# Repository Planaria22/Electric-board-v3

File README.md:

# Electric-board-v3
2026年高専祭で展示する予定の電光掲示板です

# 概要
32 * 32ドットのマトリクスが搭載されたドライバ基板を4枚横につなげることで32 * 128ドットの電光掲示板にする。ドライバ基板のジャンパ(JP1,JP2)を繋げば輝度調整も技術的には可能

# 使用技術
- MD1516C2-RG ドットマトリクスLED
  赤色と緑色のアノードコモン2色16×16LEDマトリクス。同時点灯を行うと赤緑橙の3色点灯が可能。このマトリクスをドライバ基板1枚に4個配置し、ドライバ基板を直列につなげることで32×128ドットの電光掲示板を作成する。
- 74HC595
  8bitシフトレジスタ。カスケード接続され、マイコンから送られたシリアル信号をパラレル信号へ変換する。
- PchMOSFET
  大電流が流れるアノード側スイッチング用。アクティブLowであることに注意。
- ダイナミック点灯
  電流を流すアノード(行)を変え続けることで使用するピン数と電流を削減する。
- PIO
  Programmable I/O。Raspberry Pi Picoに搭載されたピンの操作に特化したプロセッサ。PicoのCPUとは分離されており、1クロック単位でピンの入出力を制御できる。
- DMA
  Direct Memory Access。Raspberry Pi PicoのメモリとPIOをCPUを介せず高速に転送する。

# ピンアサイン
ドライバ基板の端子アサイン
## 6pinピンヘッダ・ソケット(QI)
```
+---+---+=======+---+---+
| 1 | 2 | 3 | 4 | 5 | 6 |
+---+---+---+---+---+---+
```
※デフォルトでは基板側のOEピンはプルダウンされています。使用する場合はドライバ基板のJP1かJP2、あるいは両方のジャンパを短絡してください。
1. アノードデータ
2. 赤色LEDカソードデータ
3. 緑色LEDカソードデータ
4. 74HC595 シフトレジスタクロック(SRCLK)
5. 74HC595 ストレージレジスタークロック(RCLK)
6. 74HC595 アウトプットエネーブル(OE)

## 電源ピン(VHコネクタ)
```
+=======+
| 1 | 2 |
+---+---+
```
※ドットマトリクス側が下
1. 5V電源+
2. GND電源-

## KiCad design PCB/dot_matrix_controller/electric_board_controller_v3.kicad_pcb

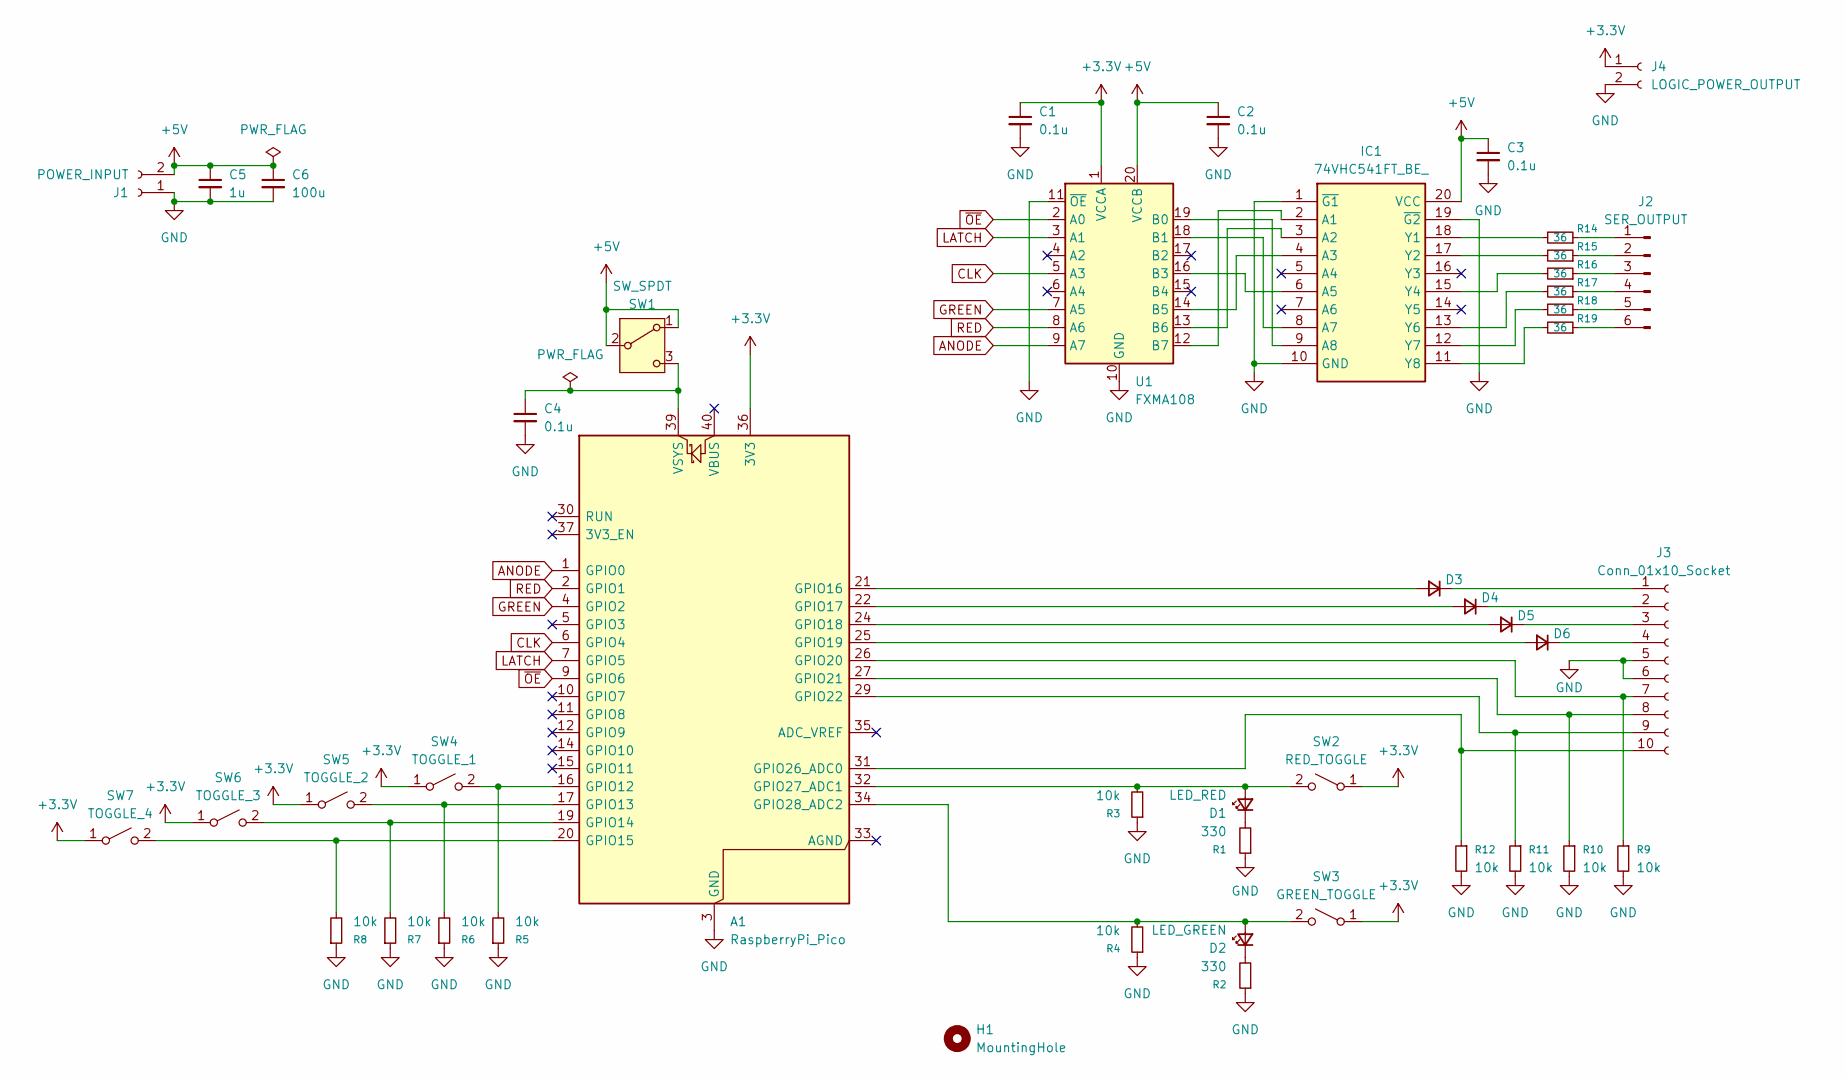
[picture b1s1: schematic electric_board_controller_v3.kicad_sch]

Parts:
A1: RaspberryPi_Pico; RaspberryPi_Pico_Common_Unspecified
C1, C2, C3, C4: 0.1u; C_Disc_D5.0mm_W2.5mm_P2.50mm
C5: 1u; C_Disc_D5.0mm_W2.5mm_P2.50mm
C6: 100u; CP_Radial_D5.0mm_P2.00mm
D1: LED_RED; LED_D2.0mm_W4.0mm_H2.8mm_FlatTop
D2: LED_GREEN; LED_D2.0mm_W4.0mm_H2.8mm_FlatTop
D3, D4, D5, D6: D_Small; D_DO-34_SOD68_P5.08mm_Vertical_AnodeUp
H1: MountingHole; MountingHole_3.2mm_M3
IC1: 74VHC541FT_BE_; 74VHC541FT(BE); Manufacturer_Part_Number 74VHC541FT(BE); Mouser Part Number 757-74VHC541FT(BE)
J1: POWER_INPUT; JST_VH_B2P-VH-B_1x02_P3.96mm_Vertical
J2: SER_OUTPUT; PinHeader_1x06_P2.54mm_Horizontal
J3: Conn_01x10_Socket; PinSocket_1x10_P2.54mm_Vertical
J4: LOGIC_POWER_OUTPUT; PinSocket_1x02_P2.54mm_Vertical
R1, R2: 330; R_Axial_DIN0207_L6.3mm_D2.5mm_P10.16mm_Horizontal
R3, R4, R5, R6, R7, R8: 10k; R_Axial_DIN0207_L6.3mm_D2.5mm_P10.16mm_Horizontal
R9, R10, R11, R12: 10k; R_0603_1608Metric
R14, R15, R16, R17, R18, R19: 36; R_0603_1608Metric
SW1: SW_SPDT; SW_Slide-03_Wuerth-WS-SLTV_10x2.5x6.4_P2.54mm
SW2: RED_TOGGLE; SW_Slide-02_Wuerth-WS-SLTV_10x2.5x6.4_P2.54mm
SW3: GREEN_TOGGLE; SW_Slide-02_Wuerth-WS-SLTV_10x2.5x6.4_P2.54mm
SW4: TOGGLE_1; SW_Slide-02_Wuerth-WS-SLTV_10x2.5x6.4_P2.54mm
SW5: TOGGLE_2; SW_Slide-02_Wuerth-WS-SLTV_10x2.5x6.4_P2.54mm
SW6: TOGGLE_3; SW_Slide-02_Wuerth-WS-SLTV_10x2.5x6.4_P2.54mm
SW7: TOGGLE_4; SW_Slide-02_Wuerth-WS-SLTV_10x2.5x6.4_P2.54mm
U1: FXMA108; FXMA108-DIP

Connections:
+3.3V: A1.36 (3V3), C1.1, J4.1, SW2.1 (A), SW3.1 (A), SW4.1 (A), SW5.1 (A), SW6.1 (A), SW7.1 (A), U1.1 (VCCA)
+5V: C2.1, C3.1, C5.1, C6.1, IC1.20 (VCC), J1.2, SW1.1 (A), SW1.2 (B), U1.20 (VCCB)
ANODE: A1.1 (GPIO0), U1.9 (A7)
CLK: A1.6 (GPIO4), U1.5 (A3)
GND: A1.3 (GND), A1.8 (GND), A1.13 (GND), A1.18 (GND), A1.23 (GND), A1.28 (GND), A1.38 (GND), C1.2, C2.2, C3.2, C4.2, C5.2, C6.2, IC1.1 (~G1), IC1.10 (GND), IC1.19 (~G2), J1.1, J3.5, J3.6, J4.2, R1.1, R2.1, R3.1, R4.1, R5.1, R6.1, R7.1, R8.1, R9.2, R10.2, R11.2, R12.2, U1.10 (GND), U1.11 (~OE)
GREEN: A1.4 (GPIO2), U1.7 (A5)
LATCH: A1.7 (GPIO5), U1.3 (A1)
unnamed: A1.16 (GPIO12), R5.2, SW4.2 (B)
unnamed: A1.17 (GPIO13), R6.2, SW5.2 (B)
unnamed: A1.19 (GPIO14), R7.2, SW6.2 (B)
unnamed: A1.20 (GPIO15), R8.2, SW7.2 (B)
unnamed: A1.21 (GPIO16), D3.2 (A)
unnamed: A1.22 (GPIO17), D4.2 (A)
unnamed: A1.24 (GPIO18), D5.2 (A)
unnamed: A1.25 (GPIO19), D6.2 (A)
unnamed: A1.26 (GPIO20), J3.7, R9.1
unnamed: A1.27 (GPIO21), J3.8, R10.1
unnamed: A1.29 (GPIO22), J3.9, R11.1
unnamed: A1.31 (GPIO26_ADC0), J3.10, R12.1
unnamed: A1.32 (GPIO27_ADC1), D1.2 (A), R3.2, SW2.2 (B)
unnamed: A1.34 (GPIO28_ADC2), D2.2 (A), R4.2, SW3.2 (B)
unnamed: A1.39 (VSYS), C4.1, SW1.3 (C)
unnamed: D1.1 (K), R1.2
unnamed: D2.1 (K), R2.2
unnamed: D3.1 (K), J3.1
unnamed: D4.1 (K), J3.2
unnamed: D5.1 (K), J3.3
unnamed: D6.1 (K), J3.4
unnamed: IC1.2 (A1), U1.12 (B7)
unnamed: IC1.3 (A2), U1.13 (B6)
unnamed: IC1.4 (A3), U1.14 (B5)
unnamed: IC1.6 (A5), U1.16 (B3)
unnamed: IC1.8 (A7), U1.18 (B1)
unnamed: IC1.9 (A8), U1.19 (B0)
unnamed: IC1.18 (Y1), R14.2
unnamed: IC1.17 (Y2), R15.2
unnamed: IC1.15 (Y4), R16.2
unnamed: IC1.13 (Y6), R17.2
unnamed: IC1.12 (Y7), R18.2
unnamed: IC1.11 (Y8), R19.2
unnamed: J2.1, R14.1
unnamed: J2.2, R15.1
unnamed: J2.3, R16.1
unnamed: J2.4, R17.1
unnamed: J2.5, R18.1
unnamed: J2.6, R19.1
RED: A1.2 (GPIO1), U1.8 (A6)
~OE: A1.9 (GPIO6), U1.2 (A0)

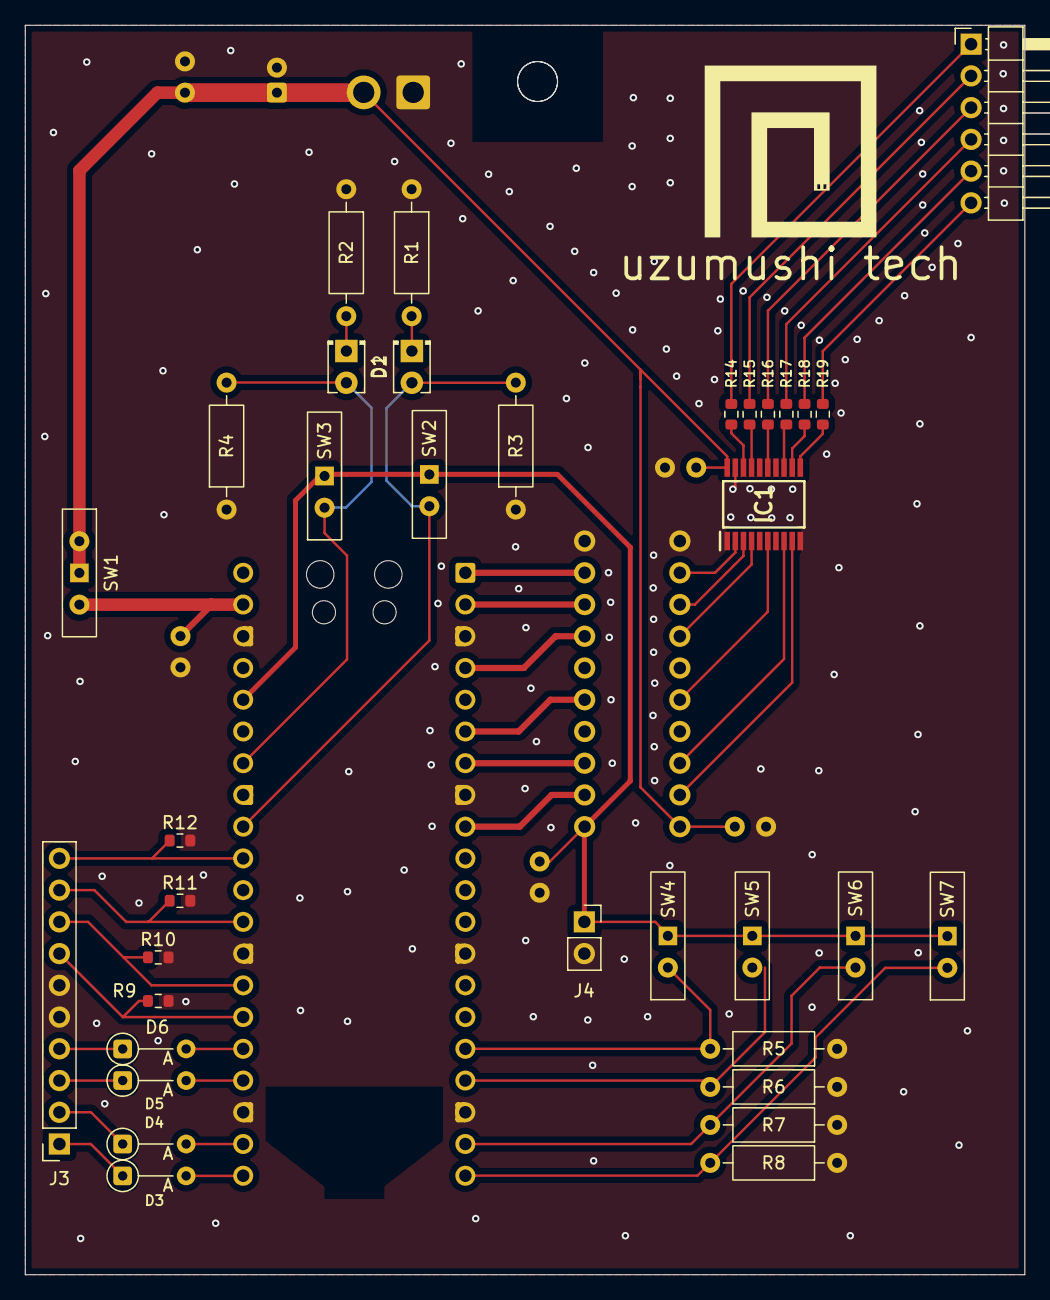
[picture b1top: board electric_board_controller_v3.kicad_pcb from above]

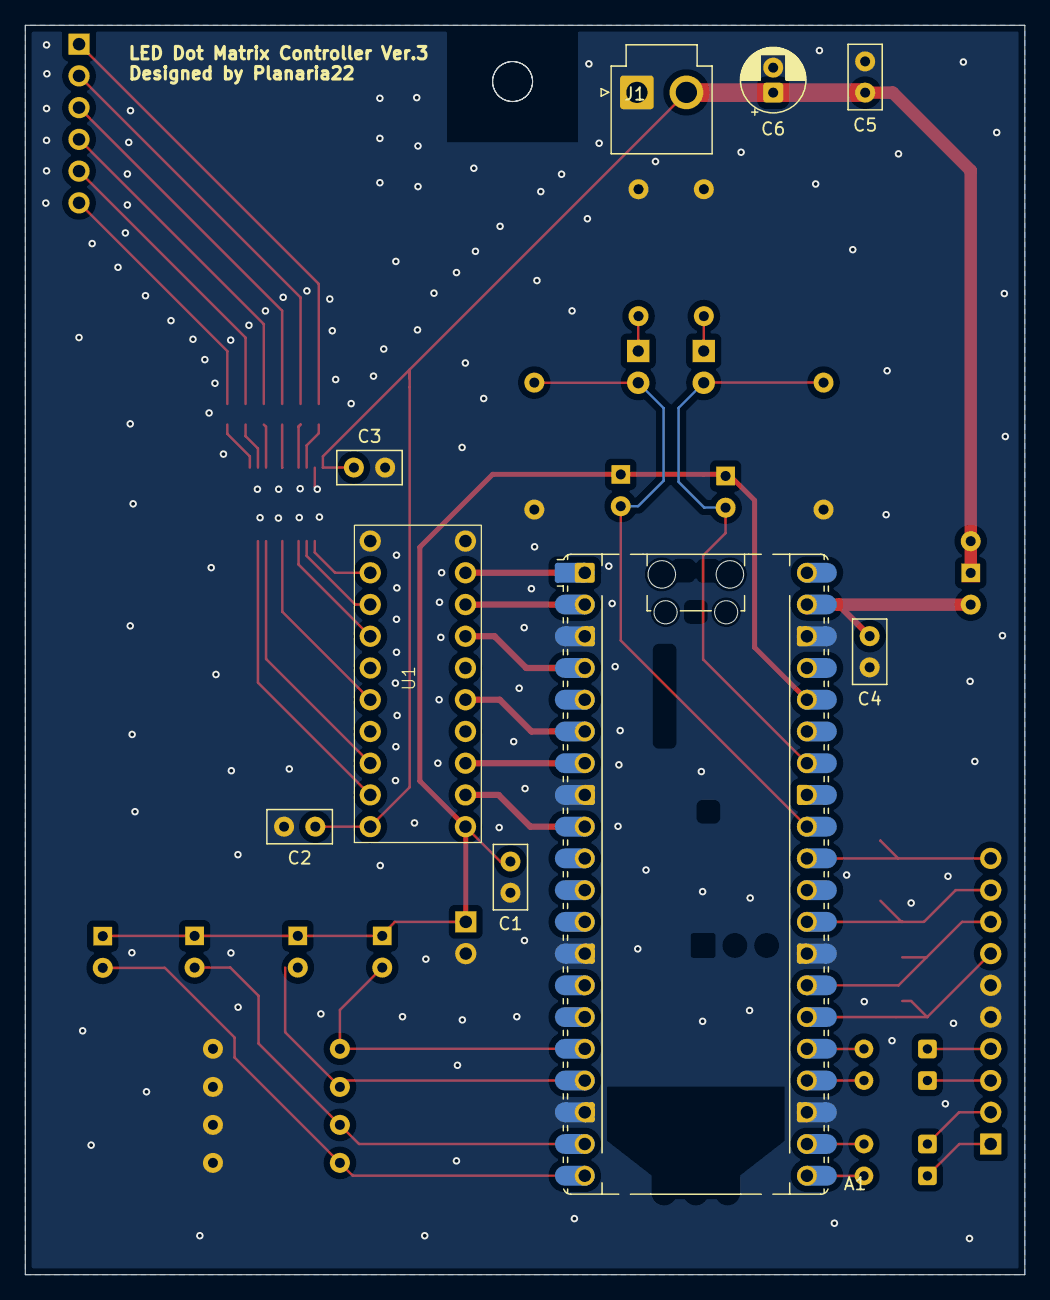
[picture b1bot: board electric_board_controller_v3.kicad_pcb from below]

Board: 2 copper layers, 80.0 x 100.0 mm, 45 parts (9 on the bottom side), 48 nets.
